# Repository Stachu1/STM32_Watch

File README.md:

# STM32 Watch

A minimalist, bare-metal wristwatch built around an STM32L0 microcontroller.
No HAL, no RTOS, no libraries. Just registers.

This is a fully custom PCB watch powered by a CR2032 coin cell, using 12 discrete LEDs arranged like a traditional analog dial. Time is displayed using LED “hands”, with additional modes for voltage, temperature, time setting, and a physics-based pendulum simulation.

## Features

### Core

- Ultra-low-power (STM32 Cortex-M0+)
- Bare-metal firmware
- RTC-based timekeeping using LSE (32.768 kHz)
- 12 discrete LEDs forming a clock dial
- Time-division multiplexing for LED control
- Two buttons for mode switching and wake-up from sleep

### Optional with IMU

- Absolute wrist tilt (AWT) wake-up
- Double tap to change LED brightness
- Pendulum simulation

## Modes

### Time display

- Hour hand: Static LED
- Minute hand: Slow fade in and out
- Subminutes (full rotation every 5min) hand: Quick fade in and out

### Statistics (Battery voltage, IMU/MCU temperature)

Battery voltage = Hour / 10 + 2V

(If hour hand is at 9 the battery voltage is 0.9V + 2V = 2.9V)

IMU/MCU temperature = Hour * 5°C + Minute * 0.1°C

(If hour hand is at 4 and minute hand is at 35 the temperature is 4 * 5°C + 35 * 0.1°C = 23.5°C)

### Time setting

Hour hand running in a circle indicated you are in the time setting mode.
Press Upper button to go into hour setting then press lower button to move the hour hand form 12 to 1, 2, 3 up to the current time. Confirm with the Upper button. Reapeat for minutes. After confirming minutes the watch will go back to Time display mode.

### Pendulum simulation

If the LEDs at 3 and 9 blink the IMU is disabled. You can enable it by pressing both buttons at once. This will enable the IMU and change mode to Time display.

IF the IMU is enbaled ther hour hand will behave like a pendulum with very low friction. I reacts to the acceleration vector in the XY plane so either tilting or moving the watch arround can cause the hour hand to move.

By double tapping the watch you can add 5 rotations a seconds to the pendulum in the current rotation direction.

If you wanna disalbe the IMU just press both buttons at once. The watch will disable the IMU and go back to the Time display mode.

## Mode changing

| *Current Mode* | *Action* | *Effect* |
|:-: | :-: | :- |
| Time display | Upper button | Change brightness |
| Time display | Double tap | Change brightness (if IMU enabled) |
| Time display | Lower button | Change mode to Stats (battery voltage) |
| Statistics | Upper button | Cycle stats (voltage/temperature) |
| Statistics | Lower button | Change mode to Time setting |
| Time setting | Upper button | Set hour/minute or confirm and change mode to Time display |
| Time setting | Lower button | Change mode to Pendulum simulation or increment hour/minute hand |
| Pendulum simulation | Upper button | Change brightness |
| Pendulum simulation | Double tap | Add +/- 5 rotations/second to the pendulum speed |
| Pendulum simulation | Upper & Lower buttons | Enable/Disable IMU (All the IMU features won't work if the IMU is disabled) |
| Pendulum simulation | Lower button | Change mode to Time display |

## Power Consumption

Tested on a CR2032 @ ~2.9V

| *Mode* | *Current* | *Wakeup* |
|:-: | :-: | :-: |
| Active (display on) | ~3mA | - |
| Stop mode (sleep) | 22uA | AWT or Buttons |
| Ultra low power (IMU off) | 5.5uA | Buttons |
| Stop mode, no IMU mounted | 2.3uA | Buttons |

## Hardware

- MCU: STM32L031
- IMU: LSM6DSM
- Timekeeping: built-in RTC with an external 32.768 kHz crystal
- Ambient light sensor (reverse-biased LED)
- Time display: 12 discrete LEDs
- Two push buttons
- Powered by a CR2032 battery

All LEDs are connected to ground through a single 100 Ω resistor, which is acceptable because only one LED is on at a time.

The RST pin has a single 100 nF capacitor, as there is an internal pull-up (~40 kΩ).

The I2C lines have external 10 kΩ pull-ups, but it would likely be possible to use weaker internal pull-ups if the frequency were reduced (not tested).

On the back side of the PCB, there are test points for SWD programming and UART debugging.

## Firmware

This project is intentionally low-level:

* Direct register access only
* No abstraction layers
* Tight control over timing and power
* Interrupt-driven architecture
* Fixed-point arithmetic (Q16.16)

### LED Driving

LEDs are updated in the IRQ handler, which runs every 100 µs. If a hand is to be shown, the LED is turned on at the beginning of its time slot and turned off when `local_step` reaches the hand’s brightness or at the end of the time slot. This approach ensures that only one LED is on at a time, limiting peak current and reducing battery voltage drop.

### Timekeeping

The STM32’s RTC runs on the low-speed external oscillator, and the time can be set by the user. Due to the high ESR of the crystal, the LSE drive strength had to be set to medium-high (`LSEDRV` in `RCC_CSR`).

### Sensors

The two interrupt pins on the LSM6DSM are used to detect double tap and absolute wrist tilt. Double tap is only available when the watch is awake, as it requires a significantly higher sampling rate.

Battery voltage is measured by reading the internal voltage reference and calculating the supply voltage. This works well, but due to the high internal resistance of the battery, the measured value is about 100 mV lower than the actual open-circuit voltage.

Temperature is measured using the IMU if it is enabled, or the internal temperature sensor of the MCU otherwise.

Ambient light sensing is not currently used, but it can be implemented by setting the pin connected to a reverse-biased LED high and then switching it to high-impedance input. The brighter it is, the faster the pin returns to a low state. Unfortunately, in very dark conditions this can take hundreds of milliseconds, which is why it is not used.

## Build System

This project uses a minimal build setup based on `build.c` and a nobuild-style workflow:
[https://github.com/tsoding/nob.h](https://github.com/tsoding/nob.h)

---

### Build

```bash
cd firmware
clang build.c -o build
./build build
```

---

### Build & Flash (ST-LINK + OpenOCD)

Solder ST-LINK SWD connections to the test points on the back. (Or just hold a pinheader on them)

```bash
./build flash
```

You can also flash the firmware using STM32CubeProgrammer.

---

## Firmware Size

```
text    data     bss     dec     hex filename
10304     56    4160   14520    38b8 firmware.elf
```

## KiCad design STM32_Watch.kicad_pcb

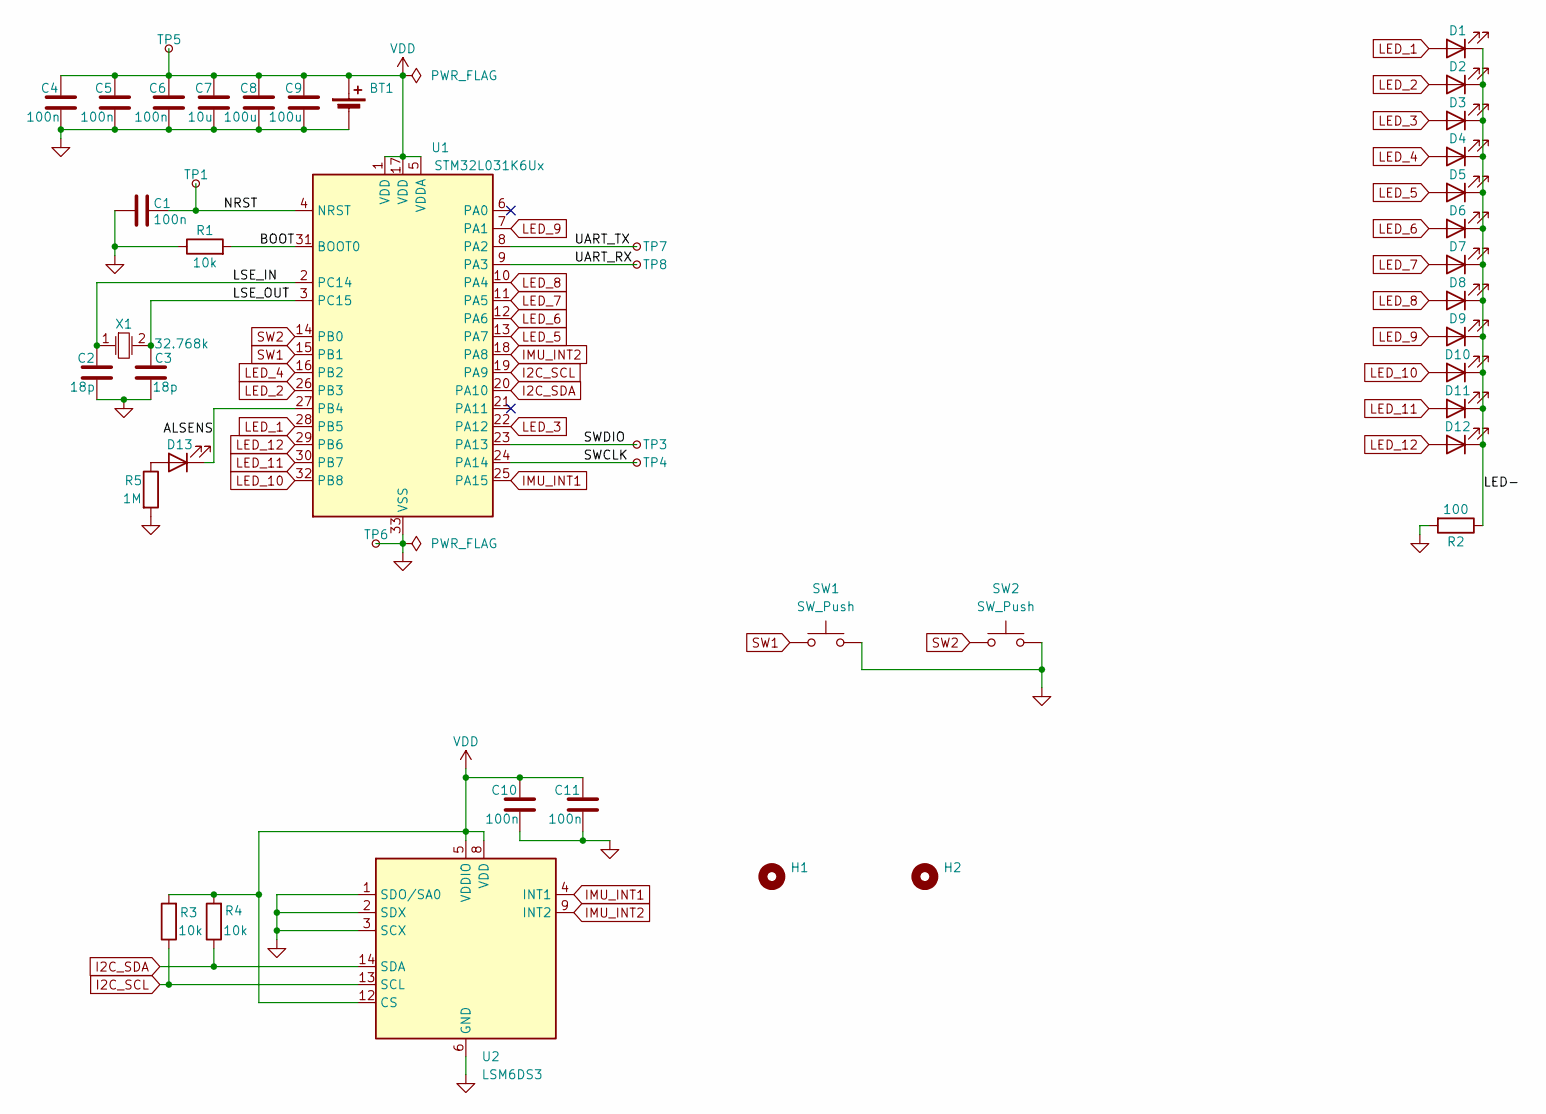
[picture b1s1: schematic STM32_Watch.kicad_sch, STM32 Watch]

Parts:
BT1: Battery_Cell; BatteryHolder_Renata_SMTU2032-LF_1x2032; LCSC C18212226
C1, C4, C5, C6, C10, C11: 100n; C_0603_1608Metric; LCSC C14663
C2, C3: 18p; C_0603_1608Metric; LCSC C1647
C7: 10u; C_0805_2012Metric; LCSC C15850
C8, C9: 100u; C_1206_3216Metric; LCSC C15008
D1, D2, D3, D4, D5, D6, D7, D8, D9, D10, D11, D12, D13: LED; LED_0603_1608Metric; LCSC C965799
H1, H2: MountingHole; StrapsConnection_20mm
R1, R3, R4: 10k; R_0603_1608Metric; LCSC C98220
R2: 100; R_0603_1608Metric; LCSC C105588
R5: 1M; R_0603_1608Metric; LCSC C105578
SW1, SW2: SW_Push; SHOU_HAN_TS24CA; LCSC C393942
TP1, TP3, TP4, TP5, TP6, TP7, TP8: TestPoint_Small; TestPoint_Pad_D1.5mm
U1: STM32L031K6Ux; QFN-32-1EP_5x5mm_P0.5mm_EP3.1x3.1mm_ThermalVias; LCSC C2969821
U2: LSM6DS3; LGA-14_3x2.5mm_P0.5mm_LayoutBorder3x4y; LCSC C967633
X1: 32.768k; Crystal_SMD_3215-2Pin_3.2x1.5mm; LCSC C5120559

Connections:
/ALSENS: D13.1 (K), U1.27 (PB4)
/BOOT: R1.2, U1.31 (BOOT0)
/LED-: D1.1 (K), D2.1 (K), D3.1 (K), D4.1 (K), D5.1 (K), D6.1 (K), D7.1 (K), D8.1 (K), D9.1 (K), D10.1 (K), D11.1 (K), D12.1 (K), R2.1
/LSE_IN: C2.2, U1.2 (PC14), X1.1
/LSE_OUT: C3.2, U1.3 (PC15), X1.2
/NRST: C1.1, TP1.1, U1.4 (NRST)
/SWCLK: TP4.1, U1.24 (PA14)
/SWDIO: TP3.1, U1.23 (PA13)
/UART_RX: TP8.1, U1.9 (PA3)
/UART_TX: TP7.1, U1.8 (PA2)
GND: BT1.2 (-), C1.2, C2.1, C3.1, C4.2, C5.2, C6.2, C7.2, C8.2, C9.2, C10.2, C11.2, R1.1, R2.2, R5.2, SW1.2, SW2.2, TP6.1, U1.33 (VSS), U2.1 (SDO/SA0), U2.2 (SDX), U2.3 (SCX), U2.6 (GND), U2.7 (GND); also elsewhere on the board
I2C_SCL: R3.1, U1.19 (PA9), U2.13 (SCL)
I2C_SDA: R4.1, U1.20 (PA10), U2.14 (SDA)
IMU_INT1: U1.25 (PA15), U2.4 (INT1)
IMU_INT2: U1.18 (PA8), U2.9 (INT2)
LED_1: D1.2 (A), U1.28 (PB5)
LED_2: D2.2 (A), U1.26 (PB3)
LED_3: D3.2 (A), U1.22 (PA12)
LED_4: D4.2 (A), U1.16 (PB2)
LED_5: D5.2 (A), U1.13 (PA7)
LED_6: D6.2 (A), U1.12 (PA6)
LED_7: D7.2 (A), U1.11 (PA5)
LED_8: D8.2 (A), U1.10 (PA4)
LED_9: D9.2 (A), U1.7 (PA1)
LED_10: D10.2 (A), U1.32 (PB8)
LED_11: D11.2 (A), U1.30 (PB7)
LED_12: D12.2 (A), U1.29 (PB6)
unnamed: D13.2 (A), R5.1
SW1: SW1.1, U1.15 (PB1)
SW2: SW2.1, U1.14 (PB0)
VDD: BT1.1 (+), C4.1, C5.1, C6.1, C7.1, C8.1, C9.1, C10.1, C11.1, R3.2, R4.2, TP5.1, U1.1 (VDD), U1.5 (VDDA), U1.17 (VDD), U2.5 (VDDIO), U2.8 (VDD), U2.12 (CS)

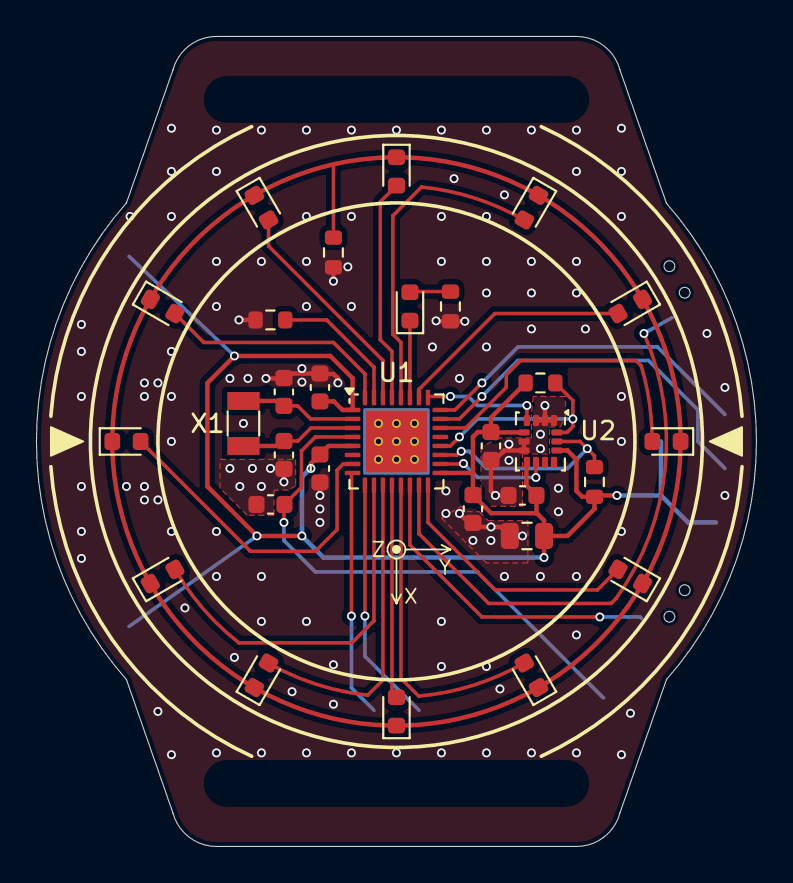
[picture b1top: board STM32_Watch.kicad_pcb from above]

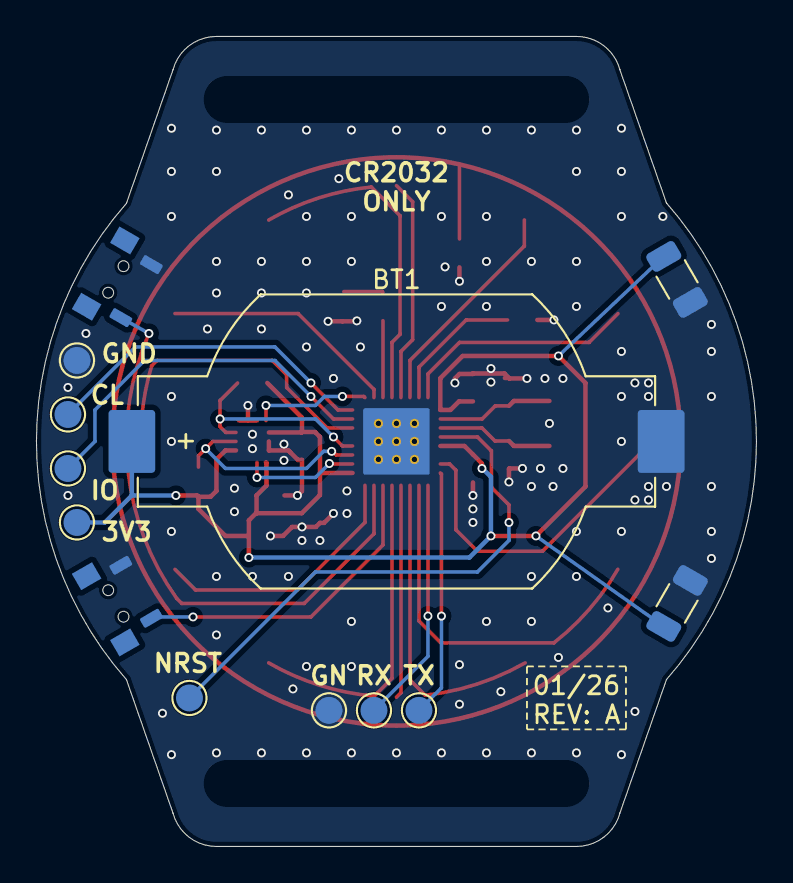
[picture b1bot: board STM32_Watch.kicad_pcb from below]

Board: 2 copper layers, 40.0 x 45.0 mm, 45 parts (13 on the bottom side), 31 nets.

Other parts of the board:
TP2: TestPoint_Small; TestPoint_Pad_D1.5mm

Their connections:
GND: TP2.1; also elsewhere on the board

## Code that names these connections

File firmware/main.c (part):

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};

const volatile LED leds[] = {
    {(volatile u32*)GPIOB, 5},   // LED 1: PB5
    {(volatile u32*)GPIOB, 3},   // LED 2: PB3
    {(volatile u32*)GPIOA, 12},  // LED 3: PA12
    {(volatile u32*)GPIOB, 2},   // LED 4: PB2
    {(volatile u32*)GPIOA, 7},   // LED 5: PA7
    {(volatile u32*)GPIOA, 6},   // LED 6: PA6
    {(volatile u32*)GPIOA, 5},   // LED 7: PA5
    {(volatile u32*)GPIOA, 4},   // LED 8: PA4
    {(volatile u32*)GPIOA, 1},   // LED 9: PA1
    {(volatile u32*)GPIOB, 8},   // LED 10: PB8
    {(volatile u32*)GPIOB, 7},   // LED 11: PB7
    {(volatile u32*)GPIOB, 6}    // LED 12: PB6
};

// Sine LUT with 64 entries for 0-360 degrees (scaled to Q32)
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// (2us @ 32MHz ~ 64 cycles)
void EXTI0_1_IRQ_Handler(void)
{
    // Check PB0 btn_down
    if (EXTI->PR & (1 << 0))
    {
        EXTI->PR = (1 << 0); // Clear the flag
    }

    // Check PB1 btn_up
    if (EXTI->PR & (1 << 1))
    {
        EXTI->PR = (1 << 1); // Clear the flag
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// EXTI Interrupt Handler for IMU AWT & Double Tap
void EXTI4_15_IRQ_Handler(void)
{
    // Check PA8 (INT2 - Wrist Tilt)
    if (EXTI->PR & (1 << 8))
    {
        EXTI->PR = (1 << 8); // Clear the flag
    }

    // Check PA15 (INT1 - Double Tap)
    if (EXTI->PR & (1 << 15))
    {
        EXTI->PR = (1 << 15); // Clear the flag
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    RCC->APB2ENR |= RCC_APB2ENR_SYSCFGEN;

    // === LEDs ===
    // Set PA1, PA4, PA5, PA6, PA7, PA12 to output (MODE = 01)
    BF_SET(GPIOA->MODER, GPIOA_MODER_MODE1, 0x1);   // PA1 as output
    BF_SET(GPIOA->MODER, GPIOA_MODER_MODE4, 0x1);   // PA4 as output
    BF_SET(GPIOA->MODER, GPIOA_MODER_MODE5, 0x1);   // PA5 as output
    BF_SET(GPIOA->MODER, GPIOA_MODER_MODE6, 0x1);   // PA6 as output
    BF_SET(GPIOA->MODER, GPIOA_MODER_MODE7, 0x1);   // PA7 as output
    BF_SET(GPIOA->MODER, GPIOA_MODER_MODE12, 0x1);  // PA12 as output
    // Set PB2, PB3, PB5, PB6, PB7, PB8 to output (MODE = 01)
    BF_SET(GPIOB->MODER, GPIOB_MODER_MODE2, 0x1);   // PB2 as output
    BF_SET(GPIOB->MODER, GPIOB_MODER_MODE3, 0x1);   // PB3 as output
    BF_SET(GPIOB->MODER, GPIOB_MODER_MODE5, 0x1);   // PB5 as output
    BF_SET(GPIOB->MODER, GPIOB_MODER_MODE6, 0x1);   // PB6 as output
    BF_SET(GPIOB->MODER, GPIOB_MODER_MODE7, 0x1);   // PB7 as output
    BF_SET(GPIOB->MODER, GPIOB_MODER_MODE8, 0x1);   // PB8 as output

    // === UART ===
    if (DEBUG)
    {
        // Set alterative pin func
        BF_SET(GPIOA->MODER, GPIOA_MODER_MODE2, 0x2);   // PA2
        BF_SET(GPIOA->MODER, GPIOA_MODER_MODE3, 0x2);   // PA3
        // Enable alterative func
        BF_SET(GPIOA->AFRL, GPIOA_AFRL_AFSEL2, 0x4);    // PA2
        BF_SET(GPIOA->AFRL, GPIOA_AFRL_AFSEL3, 0x4);    // PA3
    }

    // === I2C ===
    if (USE_IMU)
    {
    // Set alterative pin func
    BF_SET(GPIOA->MODER, GPIOA_MODER_MODE9, 0x2);   // PA9
    BF_SET(GPIOA->MODER, GPIOA_MODER_MODE10, 0x2);  // PA10
    // Set output open-drain
    GPIOA->OTYPER |= (GPIOA_OTYPER_OT9 | GPIOA_OTYPER_OT10);
    // Set high speed
    BF_SET(GPIOA->OSPEEDR, GPIOA_OSPEEDR_OSPEED9, 0x2);
    BF_SET(GPIOA->OSPEEDR, GPIOA_OSPEEDR_OSPEED10, 0x2);
    // Enable alterative func
    BF_SET(GPIOA->AFRH, GPIOA_AFRH_AFSEL9, 0x1);    // PA9
    BF_SET(GPIOA->AFRH, GPIOA_AFRH_AFSEL10, 0x1);   // PA10

    // === EXTI for IMU Interrupts ===
    // Configure PA8 and PA15 as Input
    BF_SET(GPIOA->MODER, GPIOA_MODER_MODE8, 0x0);
    BF_SET(GPIOA->MODER, GPIOA_MODER_MODE15, 0x0);
    // Map PA8 and PA15 to EXTI Line 8 and 15
    BF_SET(SYSCFG_COMP->EXTICR3, SYSCFG_COMP_EXTICR3_EXTI8, 0x0);
    BF_SET(SYSCFG_COMP->EXTICR4, SYSCFG_COMP_EXTICR4_EXTI15, 0x0);
    // Enable Rising Edge triggers
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    }

    // === Buttons ===
        // Configure PB0 and PB1 as Input
    BF_SET(GPIOB->MODER, GPIOB_MODER_MODE0, 0x0);   // PB0 as input
    BF_SET(GPIOB->MODER, GPIOB_MODER_MODE1, 0x0);   // PB1 as input
    // Enable Internal Pull-Ups
    BF_SET(GPIOB->PUPDR, GPIOB_PUPDR_PUPD0, 0x1);
    BF_SET(GPIOB->PUPDR, GPIOB_PUPDR_PUPD1, 0x1);
    // Map PB0 and PB1 to EXTI Line 0 and 1
    BF_SET(SYSCFG_COMP->EXTICR1, SYSCFG_COMP_EXTICR1_EXTI0, 0x1); // PB0
    BF_SET(SYSCFG_COMP->EXTICR1, SYSCFG_COMP_EXTICR1_EXTI1, 0x1); // PB1
    // Enable Falling Edge triggers
    EXTI->FTSR |= (EXTI_FTSR_FT0 | EXTI_FTSR_FT1); // Press
    EXTI->IMR  |= (EXTI_IMR_IM0 | EXTI_IMR_IM1);   // Unmask
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    RCC->APB1RSTR |= RCC_APB1RSTR_USART2RST;
    RCC->APB1RSTR &= ~RCC_APB1RSTR_USART2RST;

    // Set PA2 and PA3 back to Analog Mode (0x3)
    BF_SET(GPIOA->MODER, GPIOA_MODER_MODE2, 0x3);
    BF_SET(GPIOA->MODER, GPIOA_MODER_MODE3, 0x3);

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u8 Ambient_Sense(void)
{
    u32 ambl = 0;
    BF_SET(GPIOB->MODER, GPIOB_MODER_MODE4, 0x1);   // PB4 as output
    GPIOB->BSRR |= GPIOB_BSRR_BS4;
    Delay_ms(1);
    BF_SET(GPIOB->MODER, GPIOB_MODER_MODE4, 0x0);   // PB4 as input
    while (GPIOB->IDR & GPIOB_IDR_ID4 && ambl != 2080768) ambl++;
    return (u8)(255 - (ambl >> 13));
}
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    I2C1->CR1 |= I2C1_CR1_PE;

    // Set alterative pin func
    BF_SET(GPIOA->MODER, GPIOA_MODER_MODE9, 0x2);   // PA9
    BF_SET(GPIOA->MODER, GPIOA_MODER_MODE10, 0x2);  // PA10
}

// Deinit I2C
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    // Disable the I2C1 clock in RCC
    RCC->APB1ENR &= ~RCC_APB1ENR_I2C1EN;

    BF_SET(GPIOA->MODER, GPIOA_MODER_MODE9, 0x3);   // PA9 to analog
    BF_SET(GPIOA->MODER, GPIOA_MODER_MODE10, 0x3);  // PA10 to analog
}

// Write data to a slave reg @ addr, reg over I2C
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
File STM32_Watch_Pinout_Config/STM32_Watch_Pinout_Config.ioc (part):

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Mcu.Name=STM32L031K(4-6)Ux
Mcu.Package=UFQFPN32
Mcu.UserName=STM32L031K6Ux
PA10.Mode=I2C
PA10.Signal=I2C1_SDA
PA13.Mode=Serial_Wire
PA13.Signal=SYS_SWDIO
PA14.Mode=Serial_Wire
PA14.Signal=SYS_SWCLK
PA2.Mode=Asynchronous
PA2.Signal=LPUART1_TX
PA3.Mode=Asynchronous
PA3.Signal=LPUART1_RX
PA9.Mode=I2C
PA9.Signal=I2C1_SCL
PC14-OSC32_IN.Mode=LSE-External-Oscillator
PC14-OSC32_IN.Signal=RCC_OSC32_IN
PC15-OSC32_OUT.Mode=LSE-External-Oscillator
PC15-OSC32_OUT.Signal=RCC_OSC32_OUT
RCC.HSE_VALUE=8000000
RCC.SYSCLKFreq_VALUE=16000000
RCC.SYSCLKSource=RCC_SYSCLKSOURCE_HSI
board=custom

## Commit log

2025-12-14 Minimal schematics for the MCU and charging
2025-12-16 Li-po & usb charging -> CR2032 added magnetometer
2025-12-16 Added net lables & ERC fixes
2026-01-27 Added ALSENS for ambient light measurments
2026-01-28 Realigned components & Removed boot TP
2026-01-28 IMU instead of a compass
2026-01-28 Rearanged mcu pins & Routed
2026-01-29 Updated Routing & Fixed DRC problems
2026-01-29 Added silkscreen stuff
2026-01-29 Rerouted 100uF caps & Via/Pad hole size 0.2->0.3
2026-01-30 Improved routing
2026-01-31 Added GND TP & BOM file
2026-01-31 Vias dim 0.4 -> 0.5
2026-02-28 Added FW & moved PCB stuff into PCB dir
2026-02-28 Updated .gitignore
2026-02-28 Removde build files
2026-02-28 Added RTC Init Set Get
2026-02-28 Some UI ideas
2026-02-28 Some renaming bs
2026-03-01 Refactored LED control with Time-Division Multiplexing HW timers
2026-03-02 Added BTN_Init and ISR
2026-03-03 Updated menu logic
2026-03-03 Added different modes and time setting
2026-03-05 Added a particle sim that kinda works
2026-03-06 Particle sim works nicely & added comments
2026-03-06 Particle sim full rotation is q32 1 instead of 256
2026-03-07 Updated LED driver & Added brightness ctrl
2026-03-10 Added sleep mode and IMU interrupts
2026-03-11 absolute wrist tilt waking up
2026-03-14 ULP sleep 21uA @ 3V with AWT wakeup enabled
2026-03-14 Use MSI @ 4MHz instead of PLL @ 32MHz | 1.5-4mA when awake
2026-03-15 Use MSI @ ~2MHz as sysclk
2026-03-15 Tap detection only in Z axis
2026-03-15 Updated button state logic & Moved hands logic to its handler
2026-03-15 Added IMU pwr down mode | ~3mA awake, 22uA sleep, 5.5uA ULP sleep IMU off
2026-03-15 Better stats animation & Auto choose imu/mcu temp sensor
2026-03-15 Fixed I2C Init/Deinit bug
2026-03-15 third hand makes full rotation every 5min instaed of 1min
2026-03-17 Power saving & Temperature reading bug fixes
2026-03-18 Hands logic bug fixes
2026-03-19 Set LSE drive strength mid-high
2026-03-22 Updated the README
2026-03-22 Updated README, pics and modes changing
2026-03-22 Updated pics dimentions
2026-06-21 Fix formatting in temperature calculation example
    Correct formatting of temperature calculation example in README.
